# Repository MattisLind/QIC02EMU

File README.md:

# QIC02EMU

Device that is supposed to emulate a generic QIC-02 tape drive or specifically the IBM6157 tape drive. The IBM 6157 contains a Cipher 450 tape drive. But has a 37 pin DUSB interface cable rather than the 50 pin IDC type connector.

The card is supposed to plug directly into the IBM RT PC 6157 streaming tape controller board without using any cable.

Initially only reading of tape will be supported but later on writing will be implemented.

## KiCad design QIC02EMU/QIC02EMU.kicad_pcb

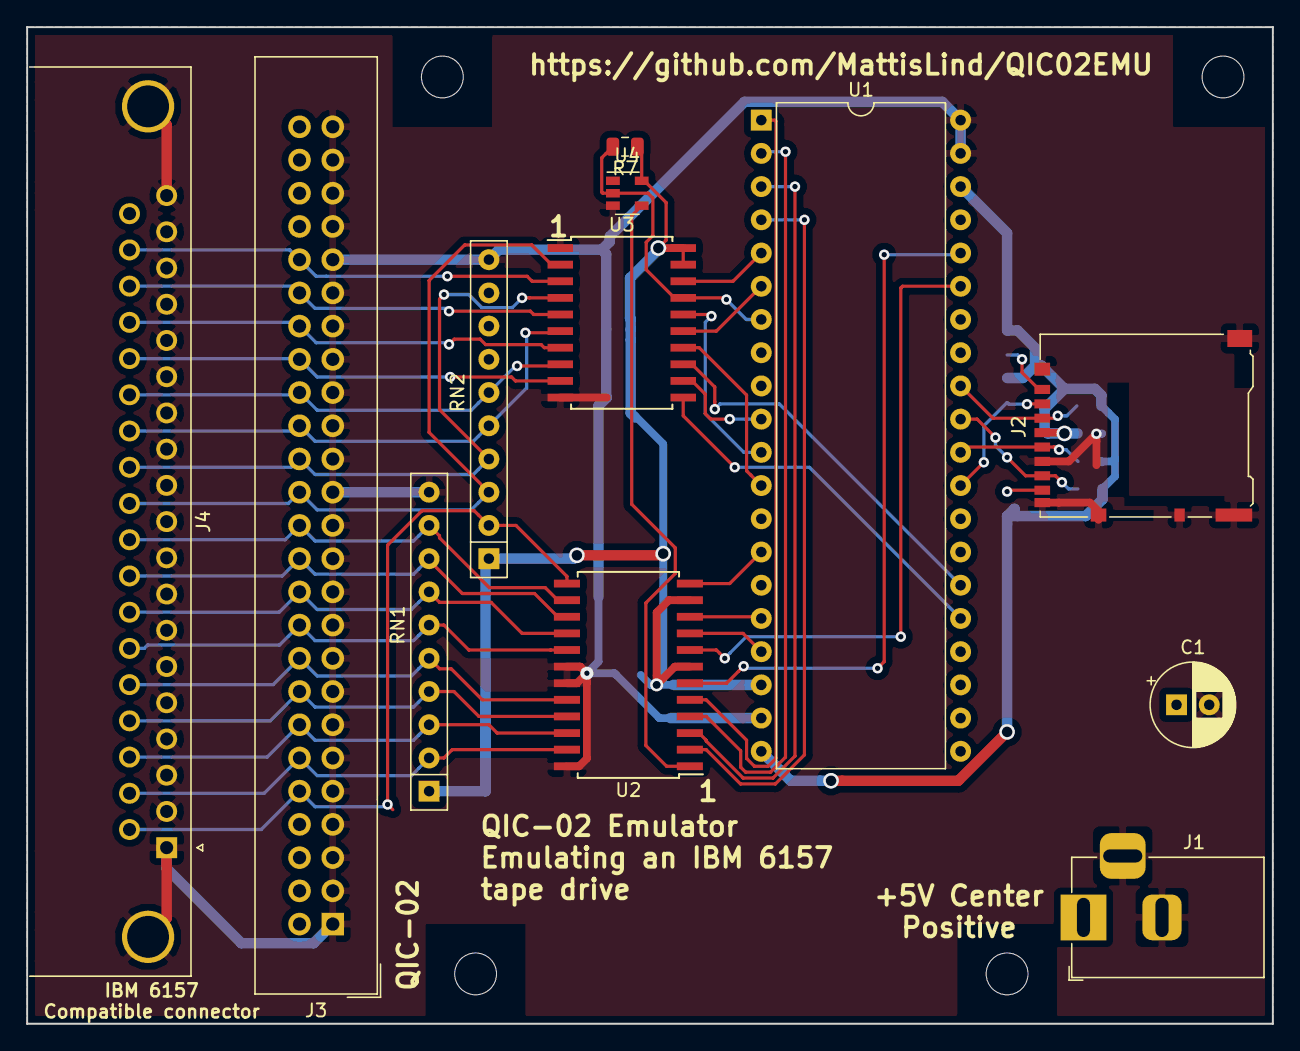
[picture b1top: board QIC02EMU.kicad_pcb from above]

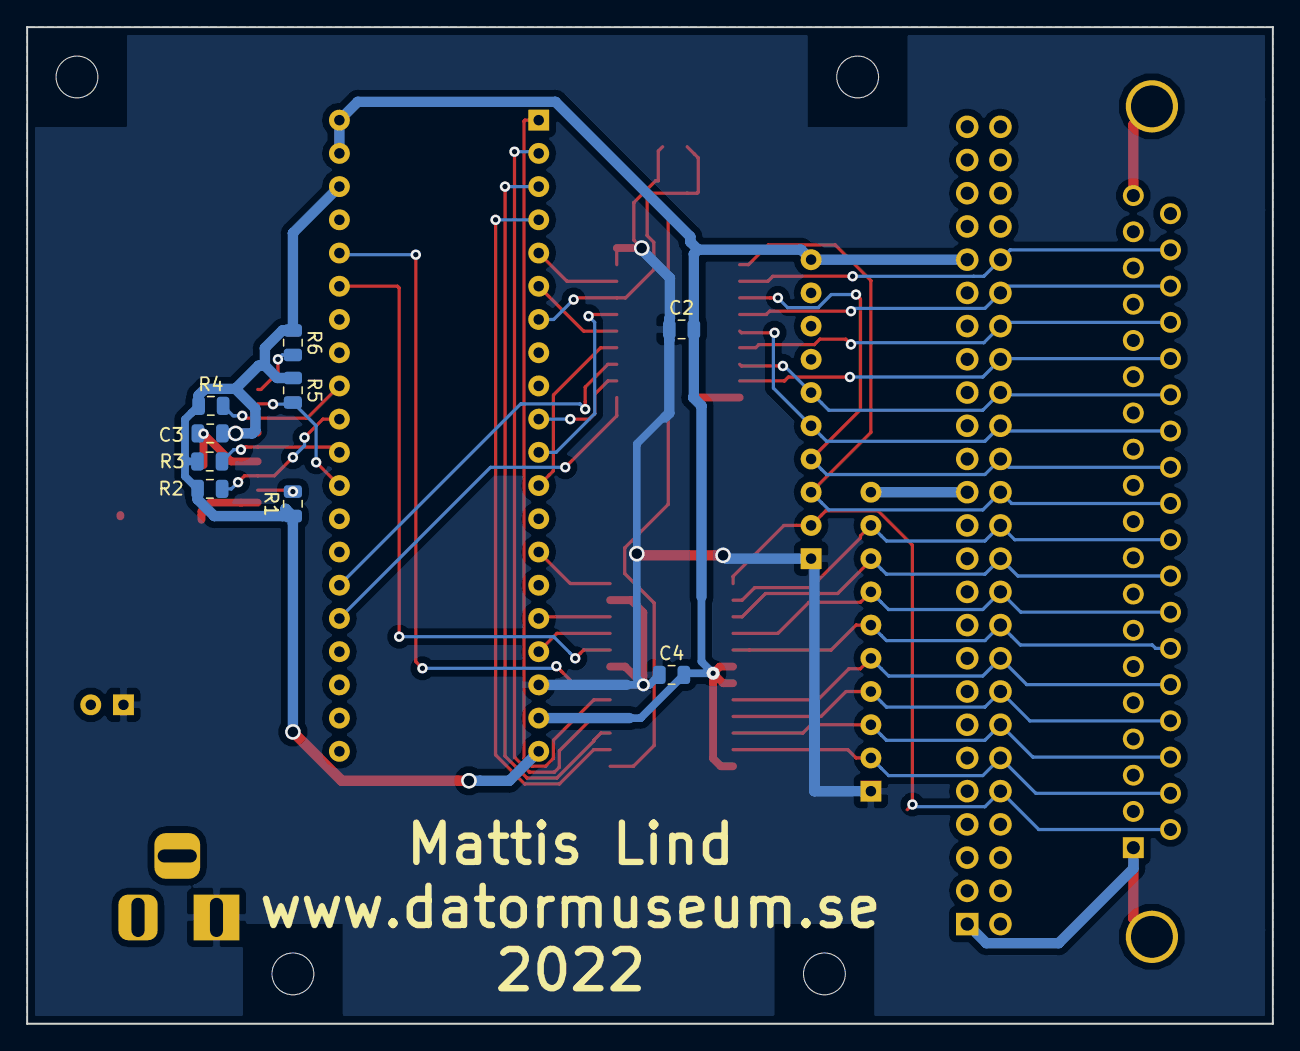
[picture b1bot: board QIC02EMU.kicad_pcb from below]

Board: 2 copper layers, 95.2 x 76.2 mm, 25 parts (9 on the bottom side), 44 nets.

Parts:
C1: 10u; CP_Radial_D6.3mm_P2.50mm
C2, C3, C4: 100n; C_0805_2012Metric
H1, H2, H3, H4: MountingHole; MountingHole_3.2mm_M3_ISO14580
J1: 2.5 mm Barrel DC JACK; BarrelJack_Horizontal
J2: Micro_SD_Card_Det; microSD_HC_Hirose_DM3AT-SF-PEJM5
J3: 50 Pin header; IDC-Header_2x25_P2.54mm_Vertical
J4: DB37_F; DSUB-37_Female_Horizontal_P2.77x2.84mm_EdgePinOffset7.70mm_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
R1, R2, R3, R4, R5, R6, R7: 68k; R_0805_2012Metric
RN1, RN2: 330/220 ohm SIP; R_Array_SIP10
U1: STM32BluePill; DIP-40_W15.24mm
U2: 74ABT657; SOIC-24W_7.5x15.4mm_P1.27mm
U3: 74ABT241; SOIC-20W_7.5x12.8mm_P1.27mm
U4: 74LVC1G04; SOT-23-5

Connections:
+3V3: C3.1, J2.4, R1.1, R2.1, R3.1, R4.1, R5.1, R6.1, U1.20, U1.38
+5V: C1.1, C2.1, C4.1, J1.1, R7.1, RN1.1, RN2.1, U1.18, U2.7, U2.11, U3.19, U3.20, U4.5
/D0: U1.16, U2.10
/D1: U1.17, U2.9
/D2: U1.35, U2.8
/D3: U1.36, U2.6
/D4: U1.1, U2.5
/D5: U1.2, U2.4
/D6: U1.3, U2.3
/D7: U1.4, U2.2
/IACK: U1.25, U3.11
/IDIR: R7.2, U1.7, U3.17, U4.2
/IEXC: U1.6, U3.15
/IONL: U1.5, U3.18
/IRDY: U1.26, U3.13
/IREQ: U1.11, U3.16
/IRST: U1.12, U3.14
/IXFR: U1.10, U3.12
/PE: U1.14, U2.12
/SD_CLK: J2.5, R3.2, U1.30
/SD_CS: J2.2, R5.2, U1.29
/SD_MISO: J2.7, R2.2, U1.31
/SD_MOSI: J2.3, R4.2, U1.32
/TR_EN: U2.1, U4.4
/~ACK: J3.36, J4.33, U3.9
/~DIR: J3.42, J4.36, U3.3
/~EXC: J3.40, J4.35, U3.5
/~HB0: J3.26, J4.28, RN1.9, U2.14
/~HB1: J3.24, J4.27, RN1.8, U2.15
/~HB2: J3.22, J4.26, RN1.7, U2.16
/~HB3: J3.20, J4.25, RN1.6, U2.17
/~HB4: J3.18, J4.24, RN1.5, U2.20
/~HB5: J3.16, J4.23, RN1.4, U2.21
/~HB6: J3.14, J4.22, RN1.3, U2.22
/~HB7: J3.12, J4.21, RN1.2, U2.23
/~HBP: J3.10, J4.20, RN2.2, U2.13
/~ONL: J3.28, J4.29, RN2.3, U3.2
/~RDY: J3.38, J4.34, U3.7
/~REQ: J3.30, J4.30, RN2.4, U3.4
/~RST: J3.32, J4.31, RN2.5, U3.6
/~XFR: J3.34, J4.32, RN2.6, U3.8
GND: C1.2, C2.2, C3.2, C4.2, J1.2, J1.3, J2.6, J2.9, J2.10, J2.11, J3.1, J3.3, J3.5, J3.7, J3.9, J3.11, J3.13, J3.15, J3.17, J3.19, J3.21, J3.23, J3.25, J3.27, J3.29, J3.31, J3.33, J3.35, J3.37, J3.39, J3.41, J3.43, J3.45, J3.47, J3.49, J4.0, J4.1, J4.2, J4.3, J4.4, J4.5, J4.6, J4.7, J4.8, J4.9, J4.10, J4.11, J4.12, J4.13, J4.14, J4.15, J4.16, J4.17, J4.18, J4.19, RN1.10, RN2.10, U1.19, U1.39, U1.40, U2.18, U2.19, U2.24, U3.1, U3.10, U4.3
unnamed: J2.1, R6.2
unnamed: J2.8, R1.2

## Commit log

2022-08-11 First draft.
2022-08-11 Added zip of all gerbers.
2022-08-12 Fixed a problem with the direction and one enable of the 241.
2022-08-15 Update with inverter.
2022-08-15 Forgot to update pdf and png.
2022-08-15 rotate 90 degrees
2022-10-09 Fixed VDD/VSS issue on SD card.
2022-10-09 Forgot the pdf file.
2022-10-09 New png file.
